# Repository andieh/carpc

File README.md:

# carpc
Digitalization of an old VW T3 Bulli

My old VW bulli needs some fancy power control. Mainly control of lights inside the van, disconnecting 5V power supply, theft control and so on. As an Add-on, my van has a "new" engine. The subaru EJ22 is also a boxer engine, but with way more power. And as this engine has some sort of diagnostics (pre-ODB2) included, it would be nice to visualize those informations as well.

so this project consists mainly of 3 parts:
- An Arduino (only for the easy for programming, code is plain C) (work in progress)
- A Raspberry Pi with Touchscreen and CarPC Kodi Interface (work in progress)
- ESP8266 IoT Chip for Wireless control of the functionality (t.b.d)

## Atmega328
This is the main part of the projects. Located in the back, this device will be always on. controlled by a 3x2 button interface, it enables the LED stripes in the back, starts the heater, turn on or off the 5V supply and so on. A horn is connected for alarm purposes. It checks the door state, or if the car was locked or not. 

## Raspberry Pi
Mainly for music, but also displays diagnostics from the engine, shows a navigation plugin or shows a rear cam. i currently implemented 3 plugins:
- GPIO service (enable rear cam, power enable, etc).
- Rear cam display: shows an overlay for the connected camera (usb analog s-video grabber and v4l2 / mplayer)
- Display of the EJ22 data (finished, but connection missing)

### Used Components
- Raspberry PI v.3
- Optocoupler ltv847 for detecting 12V / 5V voltages
- Servo for open and closing the display lid 
- Switch for detecting the state of the display lid
- electromagnet for holding the display lid
- Levelshifter TE291 for USART communication between Arduino / Raspbi
- IRLB8721 N-Channel Mosfets for LED stripes (controlled by the arduino)
- IRF9Z P-Channel (and BS107 Transistor) switch the 12V rail for the rear cam
- DHT 22 / AM2302 Temperature sensor 

### Power supply
First try was with a 18650 Battery pack, but the Raspi, including 7'' touch
screen and GPS / Stick / S-Video consumes a lot of power (about 2-3 Amps max), 
i decided to build some analog voodoo, since there is a very big battery
already included in my (every) car. There are several ways to enable the 12V
supply: 
- button on the Arduino
- the arduino itself (with a GPIO, so power is guaranteed as long it is running)
- over the ignition
If all requests were removed, a big cap (220u) is still providing power for
some time (>10s) for the N-PMOS gate to ensure the Raspi has enough time to
shutdown. There are 3 MP1584 Buck Converter (step down) modules, which power the 
raspberry itself, one for the display and one for the USB hub. 

## ESP8266
Nice small thing to play with. Is directly connected to the EJ22 engine and sends data via broadcast. but currently not work in progress. to be implemented later.

Schematics (created with kicad) will be updated on time, details and more to come soon.

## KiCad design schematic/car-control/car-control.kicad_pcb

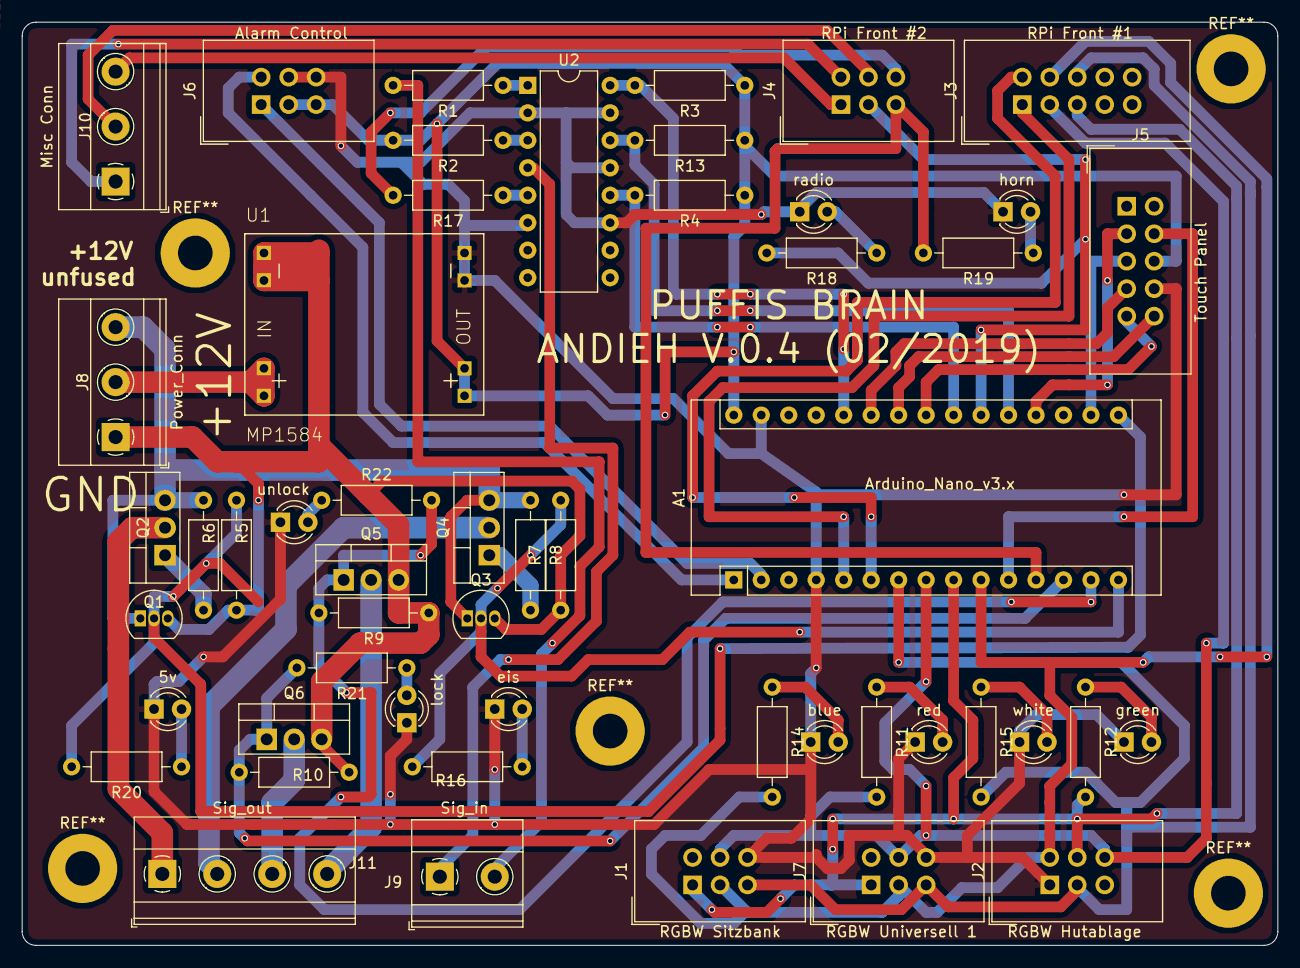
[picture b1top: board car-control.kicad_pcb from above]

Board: 2 copper layers, 116.1 x 85.3 mm, 52 parts (0 on the bottom side), 53 nets.

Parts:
5v: act_5v; LED_D3.0mm_Clear
A1: Arduino_Nano_v3.x; Arduino_Nano
J1: RGBW Sitzbank; IDC-Header_2x03_P2.54mm_Vertical
J2: RGBW Hutablage; IDC-Header_2x03_P2.54mm_Vertical
J3: RPi Front #1; IDC-Header_2x05_P2.54mm_Vertical
J4: RPi Front #2; IDC-Header_2x03_P2.54mm_Vertical
J5: Touch Panel; IDC-Header_2x05_P2.54mm_Vertical
J6: Alarm Control; IDC-Header_2x03_P2.54mm_Vertical
J7: RGBW Universell 1; IDC-Header_2x03_P2.54mm_Vertical
J8: Power_Conn; TerminalBlock_Phoenix_MKDS-1,5-3-5.08_1x03_P5.08mm_Horizont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
J9: Sig_in; TerminalBlock_Phoenix_MKDS-1,5-2-5.08_1x02_P5.08mm_Horizont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
J10: Misc Conn; TerminalBlock_Phoenix_MKDS-1,5-3-5.08_1x03_P5.08mm_Horizont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
J11: Sig_out; TerminalBlock_Phoenix_MKDS-1,5-4-5.08_1x04_P5.08mm_Horizont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
Q1, Q3: BS107; TO-92_Inline
Q2, Q4: IRF9540N; TO-220-3_Vertical
Q5, Q6: IRLB8721PBF; TO-220-3_Vertical
R1, R2, R11, R12, R15, R16, R18, R19, R20, R21, R22: 220; R_Axial_DIN0207_L6.3mm_D2.5mm_P10.16mm_Horizontal
R3, R4, R13: 4.7k; R_Axial_DIN0207_L6.3mm_D2.5mm_P10.16mm_Horizontal
R5, R6, R7, R8, R9, R10: 10k; R_Axial_DIN0207_L6.3mm_D2.5mm_P10.16mm_Horizontal
R14: 120; R_Axial_DIN0207_L6.3mm_D2.5mm_P10.16mm_Horizontal
R17: 680; R_Axial_DIN0207_L6.3mm_D2.5mm_P10.16mm_Horizontal
U1: MP1584; SG053-SZ
U2: LTV-847; DIP-16_W7.62mm
blue: blue; LED_D3.0mm_Clear
eis: act_eis; LED_D3.0mm_Clear
green: green; LED_D3.0mm_Clear
horn: horn; LED_D3.0mm_Clear
lock: lock; LED_D3.0mm_Clear
radio: radio; LED_D3.0mm_Clear
red: red; LED_D3.0mm_Clear
unlock: unlock; LED_D3.0mm_Clear
white: white; LED_D3.0mm_Clear

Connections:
/220_avail: J9.2, R1.2
/220_led: A1.19, J5.3
/GND: 5v.1, A1.4, A1.29, J1.6, J2.1, J5.8, J6.4, J6.6, J7.6, U1.5, U1.6, U2.2, U2.6, U2.11, U2.13, U2.15, blue.1, eis.1, green.1, horn.1, lock.1, radio.1, red.1, unlock.1, white.1
/RX: A1.2, J6.1
/SCL: A1.23, J5.9
/SDA: A1.24, J5.10
/TX: A1.1, J6.2
/VDD: A1.30, J5.6, J6.3, J6.5, R2.2, R3.1, R4.1, R13.1, U1.7, U1.8
/analog_light: A1.25, J5.7
/cam_1_g: J4.1, J10.3
/cam_2_r: J4.2, J10.1
/cam_3_s: J4.4, J10.2
/door_gnd: J9.1, U2.4
/inp_12v: J8.2, U1.3, U1.4
/inp_12v_unfused: J8.3, Q1.1, Q2.3, Q3.1, Q4.3, R6.1, R8.1
/inp_gnd: J8.1, Q1.3, Q3.3, Q5.3, Q6.3, R5.1, R7.1, R9.1, R10.1, U1.1, U1.2
/lock_car: J11.3, Q6.2
/power_5v: J11.1, Q2.2
/power_eis: J11.2, Q4.2
/pwm_touch: A1.11, J5.4
/sig_5v: A1.16, Q1.2, R5.2, R20.2
/sig_220v: A1.26, R3.2, U2.16
/sig_b: A1.10, J1.3, J2.2, J3.4, J7.3, R14.2
/sig_door: A1.20, R13.2, U2.14
/sig_eis: A1.15, Q3.2, R7.2, R16.2
/sig_g: A1.9, J1.1, J2.4, J3.5, J7.1, R12.2
/sig_horn: A1.12, J4.5, R19.2
/sig_lock: A1.13, Q6.1, R10.2, R21.2
/sig_lock_inp: J4.6, R17.2
/sig_locked: A1.22, R4.2, U2.12
/sig_r: A1.8, J1.4, J2.6, J3.3, J7.4, R11.2
/sig_radio: A1.21, J4.3, R18.2
/sig_unlock: A1.14, Q5.1, R9.2, R22.2
/sig_w: A1.7, J1.5, J2.3, J3.6, J7.5, R15.2
/soft_RX: A1.5, J3.1
/soft_TX: A1.6, J3.2
/unlock_car: J11.4, Q5.2
/v33: A1.17, J5.5
unnamed: R11.1, red.2
unnamed: R12.1, green.2
unnamed: R14.1, blue.2
unnamed: R15.1, white.2
unnamed: R16.1, eis.2
unnamed: R19.1, horn.2
unnamed: R18.1, radio.2
unnamed: 5v.2, R20.1
unnamed: R21.1, lock.2
unnamed: R22.1, unlock.2
unnamed: Q2.1, R6.2
unnamed: Q4.1, R8.2
unnamed: R1.1, U2.1
unnamed: R2.1, U2.3
unnamed: R17.1, U2.5

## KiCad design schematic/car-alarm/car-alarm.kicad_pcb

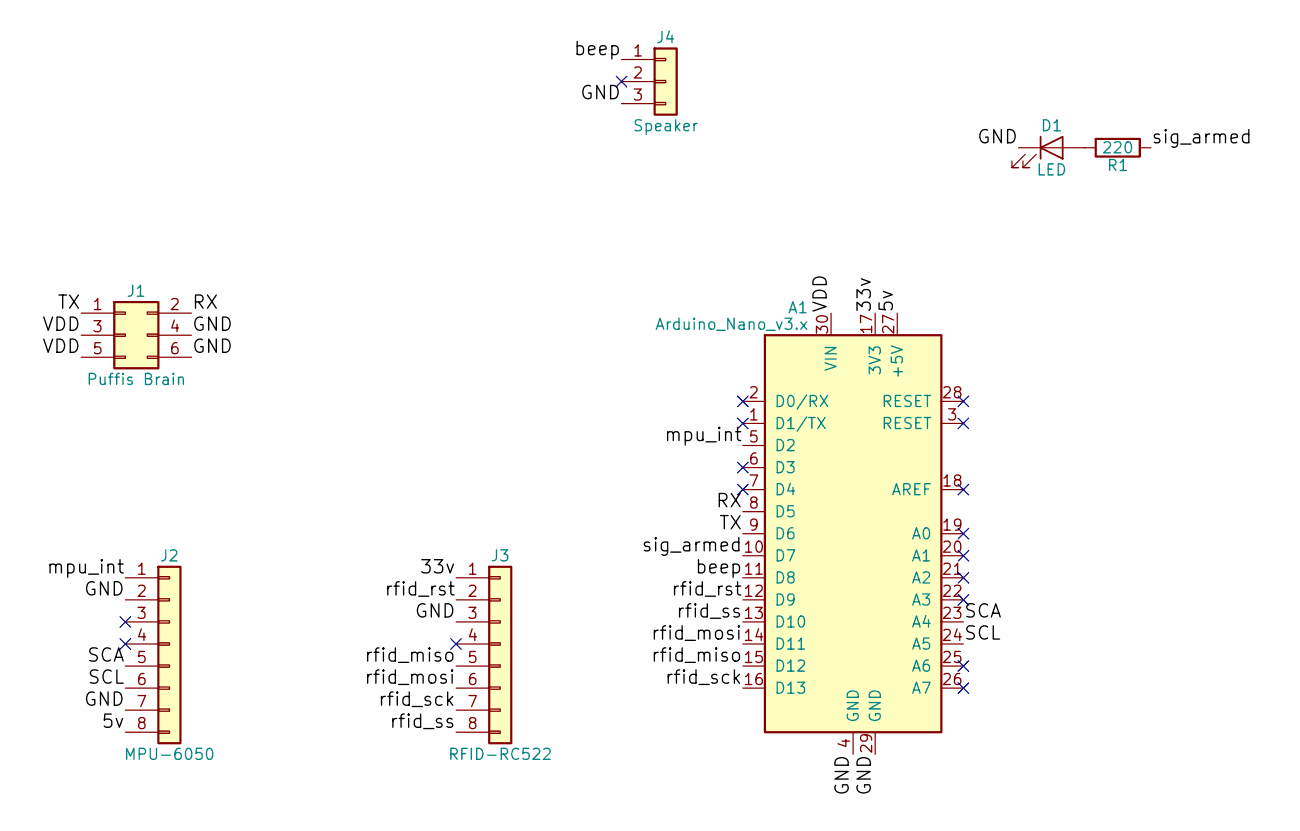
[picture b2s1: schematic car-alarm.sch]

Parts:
A1: Arduino_Nano_v3.x; Arduino_Nano
D1: LED; LED_D5.0mm_Clear
J1: Puffis Brain; IDC-Header_2x03_P2.54mm_Vertical
J2: MPU-6050; PinHeader_1x08_P2.54mm_Vertical
J3: RFID-RC522; PinHeader_1x08_P2.54mm_Vertical
J4: Speaker; PinHeader_1x03_P2.54mm_Vertical
R1: 220; R_Axial_DIN0207_L6.3mm_D2.5mm_P10.16mm_Horizontal

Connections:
/5v: A1.27 (+5V), J2.8
/33v: A1.17 (3V3), J3.1
/GND: A1.4 (GND), A1.29 (GND), D1.1 (K), J1.4, J1.6, J2.2, J2.7, J3.3, J4.3
/RX: A1.8 (D5), J1.2
/SCA: A1.23 (A4), J2.5
/SCL: A1.24 (A5), J2.6
/TX: A1.9 (D6), J1.1
/VDD: A1.30 (VIN), J1.3, J1.5
/beep: A1.11 (D8), J4.1
/mpu_int: A1.5 (D2), J2.1
/rfid_miso: A1.15 (D12), J3.5
/rfid_mosi: A1.14 (D11), J3.6
/rfid_rst: A1.12 (D9), J3.2
/rfid_sck: A1.16 (D13), J3.7
/rfid_ss: A1.13 (D10), J3.8
/sig_armed: A1.10 (D7), R1.1
unnamed: D1.2 (A), R1.2

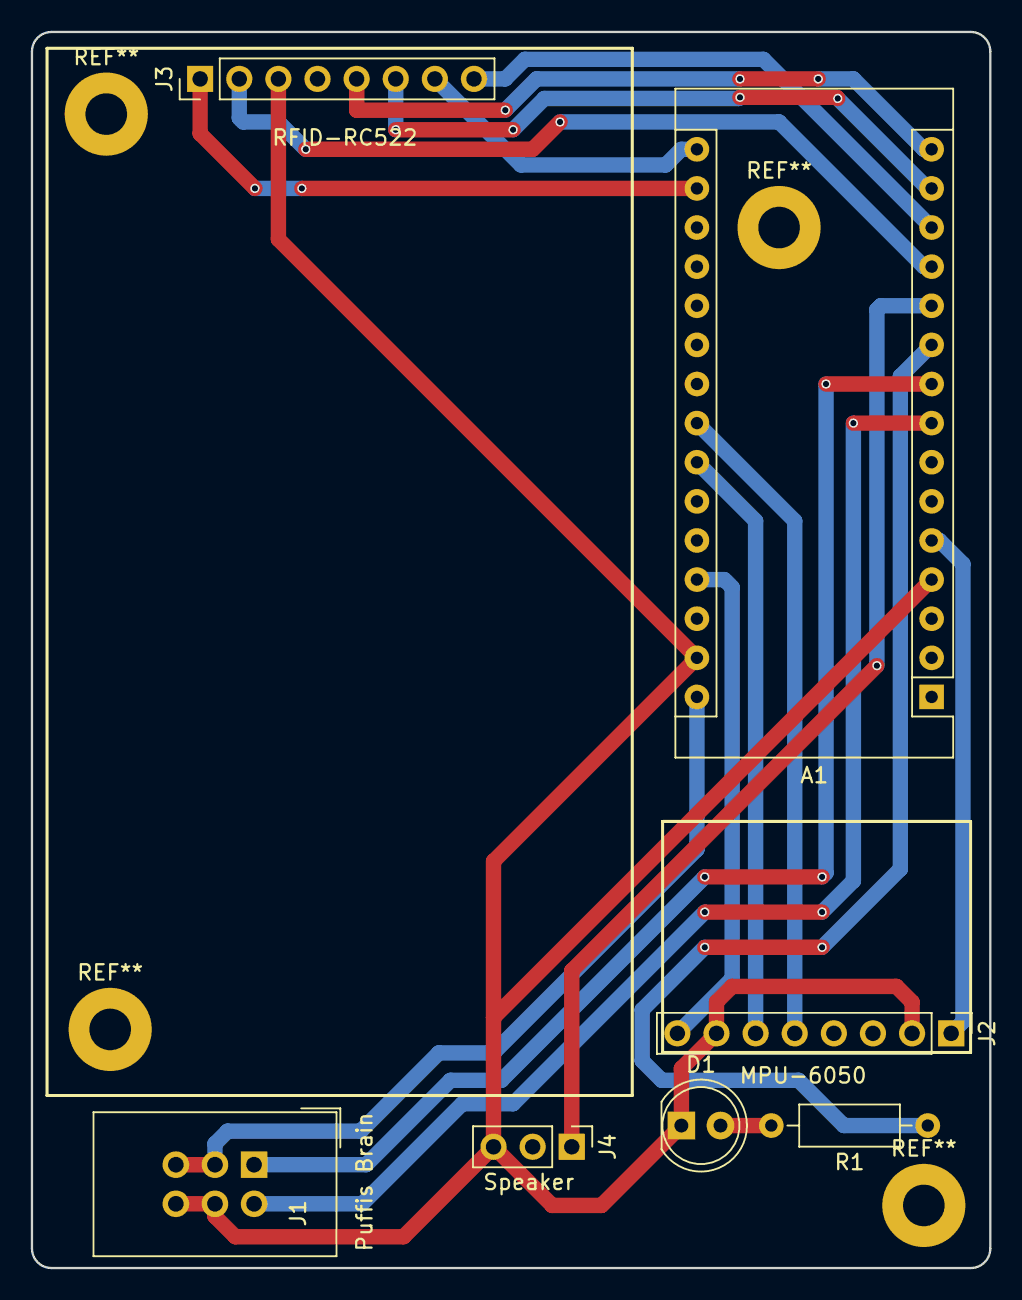
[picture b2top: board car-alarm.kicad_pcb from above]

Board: 2 copper layers, 62.2 x 80.3 mm, 7 parts (0 on the bottom side), 17 nets.

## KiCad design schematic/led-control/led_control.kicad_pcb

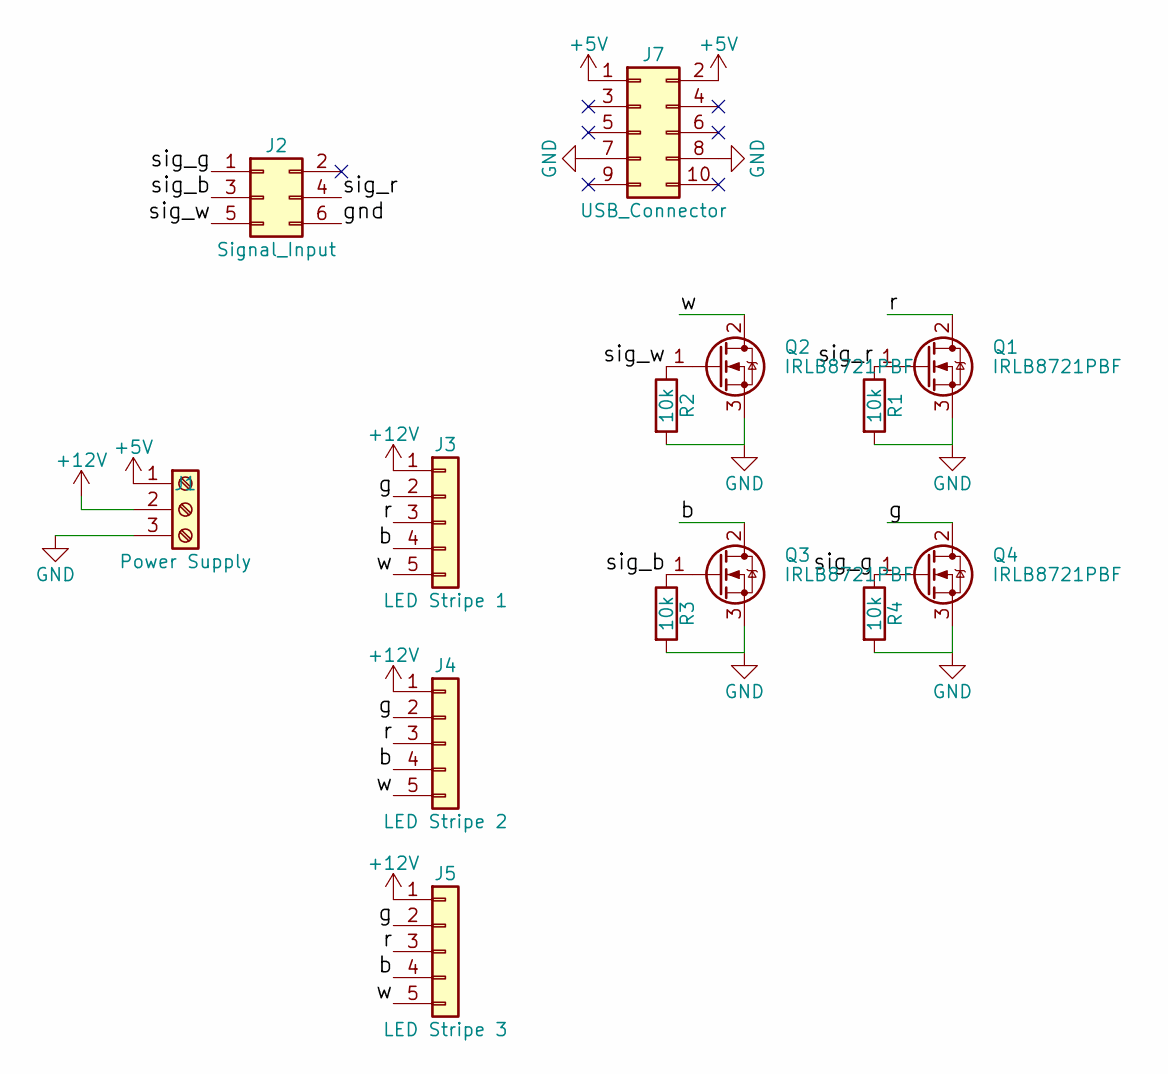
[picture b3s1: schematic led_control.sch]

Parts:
J1: Power Supply; TerminalBlock_Phoenix_MKDS-1,5-3-5.08_1x03_P5.08mm_Horizont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
J2: Signal_Input; IDC-Header_2x03_P2.54mm_Vertical
J3: LED Stripe 1; PinHeader_1x05_P2.54mm_Vertical
J4: LED Stripe 2; PinHeader_1x05_P2.54mm_Vertical
J5: LED Stripe 3; PinHeader_1x05_P2.54mm_Vertical
J7: USB_Connector; IDC-Header_2x05_P2.54mm_Vertical
Q1, Q2, Q3, Q4: IRLB8721PBF; TO-220-3_Vertical
R1, R2, R3, R4: 10k; R_Axial_DIN0411_L9.9mm_D3.6mm_P12.70mm_Horizontal

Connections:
+5V: J1.1, J7.1, J7.2
+12V: J1.2, J3.1, J4.1, J5.1
/b: J3.4, J4.4, J5.4, Q3.2 (D)
/g: J3.2, J4.2, J5.2, Q4.2 (D)
/r: J3.3, J4.3, J5.3, Q1.2 (D)
/sig_b: J2.3, Q3.1 (G), R3.1
/sig_g: J2.1, Q4.1 (G), R4.1
/sig_r: J2.4, Q1.1 (G), R1.1
/sig_w: J2.5, Q2.1 (G), R2.1
/w: J3.5, J4.5, J5.5, Q2.2 (D)
GND: J1.3, J2.6, J7.7, J7.8, Q1.3 (S), Q2.3 (S), Q3.3 (S), Q4.3 (S), R1.2, R2.2, R3.2, R4.2

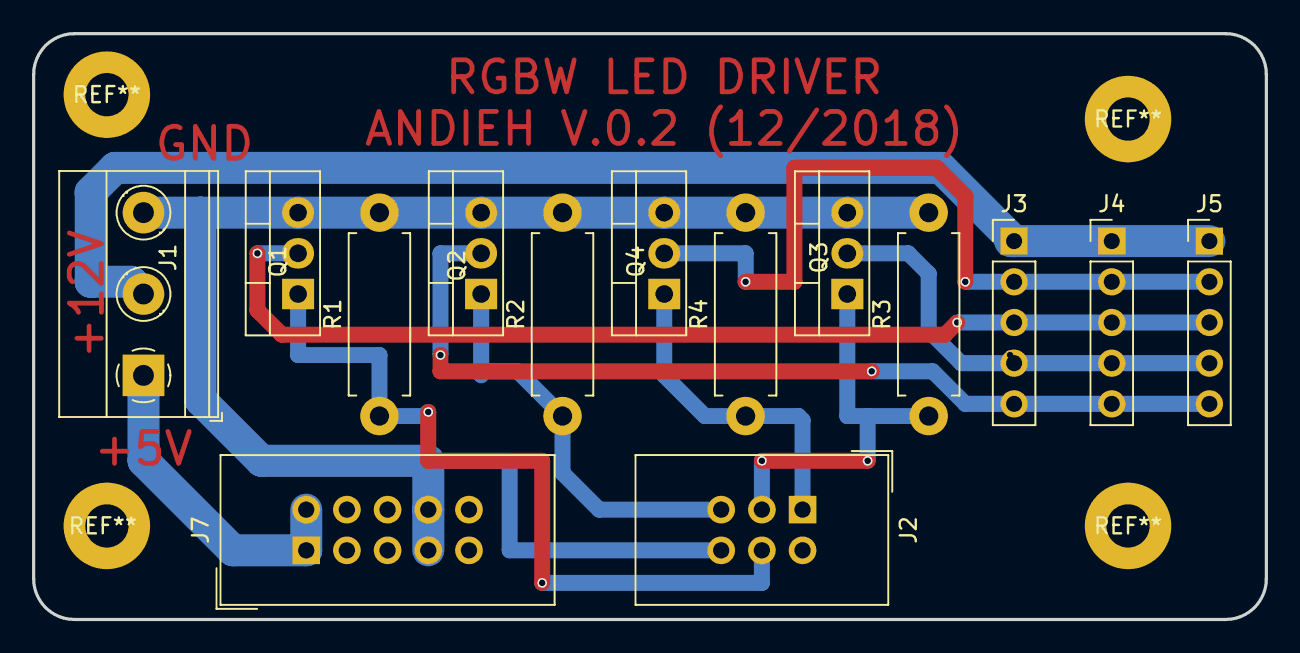
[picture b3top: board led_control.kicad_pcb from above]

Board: 2 copper layers, 77.0 x 36.6 mm, 14 parts (0 on the bottom side), 11 nets.

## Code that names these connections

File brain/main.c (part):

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 *
 * PORTB
 * PB0  D8   >  touch_pwm   Dims the LEDs on the Touch board 
 * PB1  D9   >  sig_horn    For alarm purpurses, enable horn. 
 *                          \Todo: own board for power control?
 * PB2  D10  >  sig_lock    Locks the car using a N-Transistor
 * PB3  D11  >  NEW: sig_unlock
 *                   replaced sig_220v    check if 220V are available. 5V is read
 *                          by the optocoppler
 * PB4  D12  >  sig_eis     Enables the 12V P-Transistor output for 
 *                          the EisEx.
 * PB5  D13  >  sig_5v      Enables 12V for the 5V rail.
 *
 * PORTC
 * PC0  A0   >  NEW: 220_led
 *                   replaced analog_light  measure voltage for dimming touch LEDs
 * PC1  A1   <  sig_door      doors were opened (ground enabled)
 * PC2  A2   >  sig_radio     enabled radio in the front
 * PC3  A3   <  sig_locked    high if car is locked
 * PC4  A4   >  NEW: SCL      
 *                   replaced 220_led       indicates 220V are available 
 * PC5  A5   >  NEW: SCA      
 *                   replaced SCL i2c for touch panel
 * PC6  A6   <  NEW: analog_light   
 *                   replaced SDA i2c for touch panel
 * PC7  A7   <  NEW: sig_220v
 *                   replaced sig_unlock    Unlocks the car using a N-Transistor
 *
 * PORTD
 * PD0  RX   <  RX          Receive Data from the Arduino
 * PD1  TX   >  TX          Trasmit Data to the Alarm Arduino
 * PD2  D2   <  soft_RX     Receive Data from the RPI 
 *                          \Todo: implement this!
 * PD3  D3   >  soft TX     Transmit Data to the RPI 
 *                          \Todo: implement this!
 * PD4  D4   >  sig_w       LED Stripe, white LED
 * PD5  D5   >  sig_r       LED Stripe, red LED
 * PD6  D6   >  sig_g       LED Stripe, green LED
 * PD7  D7   >  sig_b       LED Stripe, blue LED
 *
 */

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        led_color[LED_COLOR_RED] = 0;
    }

    set_output(&OUT_5V_PORT, OUT_5V_PIN, sig_5v);
    set_output(&OUT_EIS_PORT, OUT_EIS_PIN, sig_eis);
    set_output(&OUT_RADIO_PORT, OUT_RADIO_PIN, sig_radio);
    set_output(&OUT_220_PORT, OUT_220_PIN, sig_220_out);

    if (lock_cnt == 0) {
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
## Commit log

2017-11-17 initial
2017-11-17 cleanup
2017-11-17 working with UART and PWM
2017-11-27 dimming, and button are working
2017-11-27 more new files
2017-11-27 ok, next step
2017-11-28 add tuerkontakt
2017-11-28 uff, it was late yesterday
2017-11-28 new button stuff
2017-12-02 some more python stuff
2017-12-02 new stuff for fake data
2017-12-03 kodi plugin started
2017-12-04 jiiiiipppii
2017-12-05 some useability stuff
2017-12-06 Create README.md
    ja genau
2017-12-13 combined actual state with led and button registers
2017-12-16 arduino and pi working over softuart
2017-12-16 ok, did some more stuff
2017-12-17 ding dong duedeldu
2017-12-18 cleanup and more python examples
2017-12-18 add new gpio script
2017-12-20 i did something
2017-12-20 alarm added, temp reader
2017-12-20 oehm alarm added
2017-12-20 minor
2017-12-21 more stuff to come
2017-12-22 add new system scripts, new power circuit
2017-12-23 jeah, rear camera working
2017-12-25 white LED working, some cleanup
2017-12-31 more with white LED
2017-12-31 set rgb color over uart, fix power dialog
2018-01-02 white working, detetction of door open and lock implemented
2018-01-07 motor control added on boot up
2018-01-08 more readme, more checks for the display opener
2018-01-09 add first schematic view for raspberry pi layout
2018-01-09 readme
2018-01-09 updated readme file
2018-01-09 added power schematic
2018-01-09 readme update
2018-01-09 minor in power schematic
2019-01-14 ok, lets go again
2019-01-17 more in LED stuff, connection in/outputs mostly working
2019-01-21 new touch interface working
2019-01-23 added more schematics
2019-02-15 i really have no glue what i have done since the last checkin
